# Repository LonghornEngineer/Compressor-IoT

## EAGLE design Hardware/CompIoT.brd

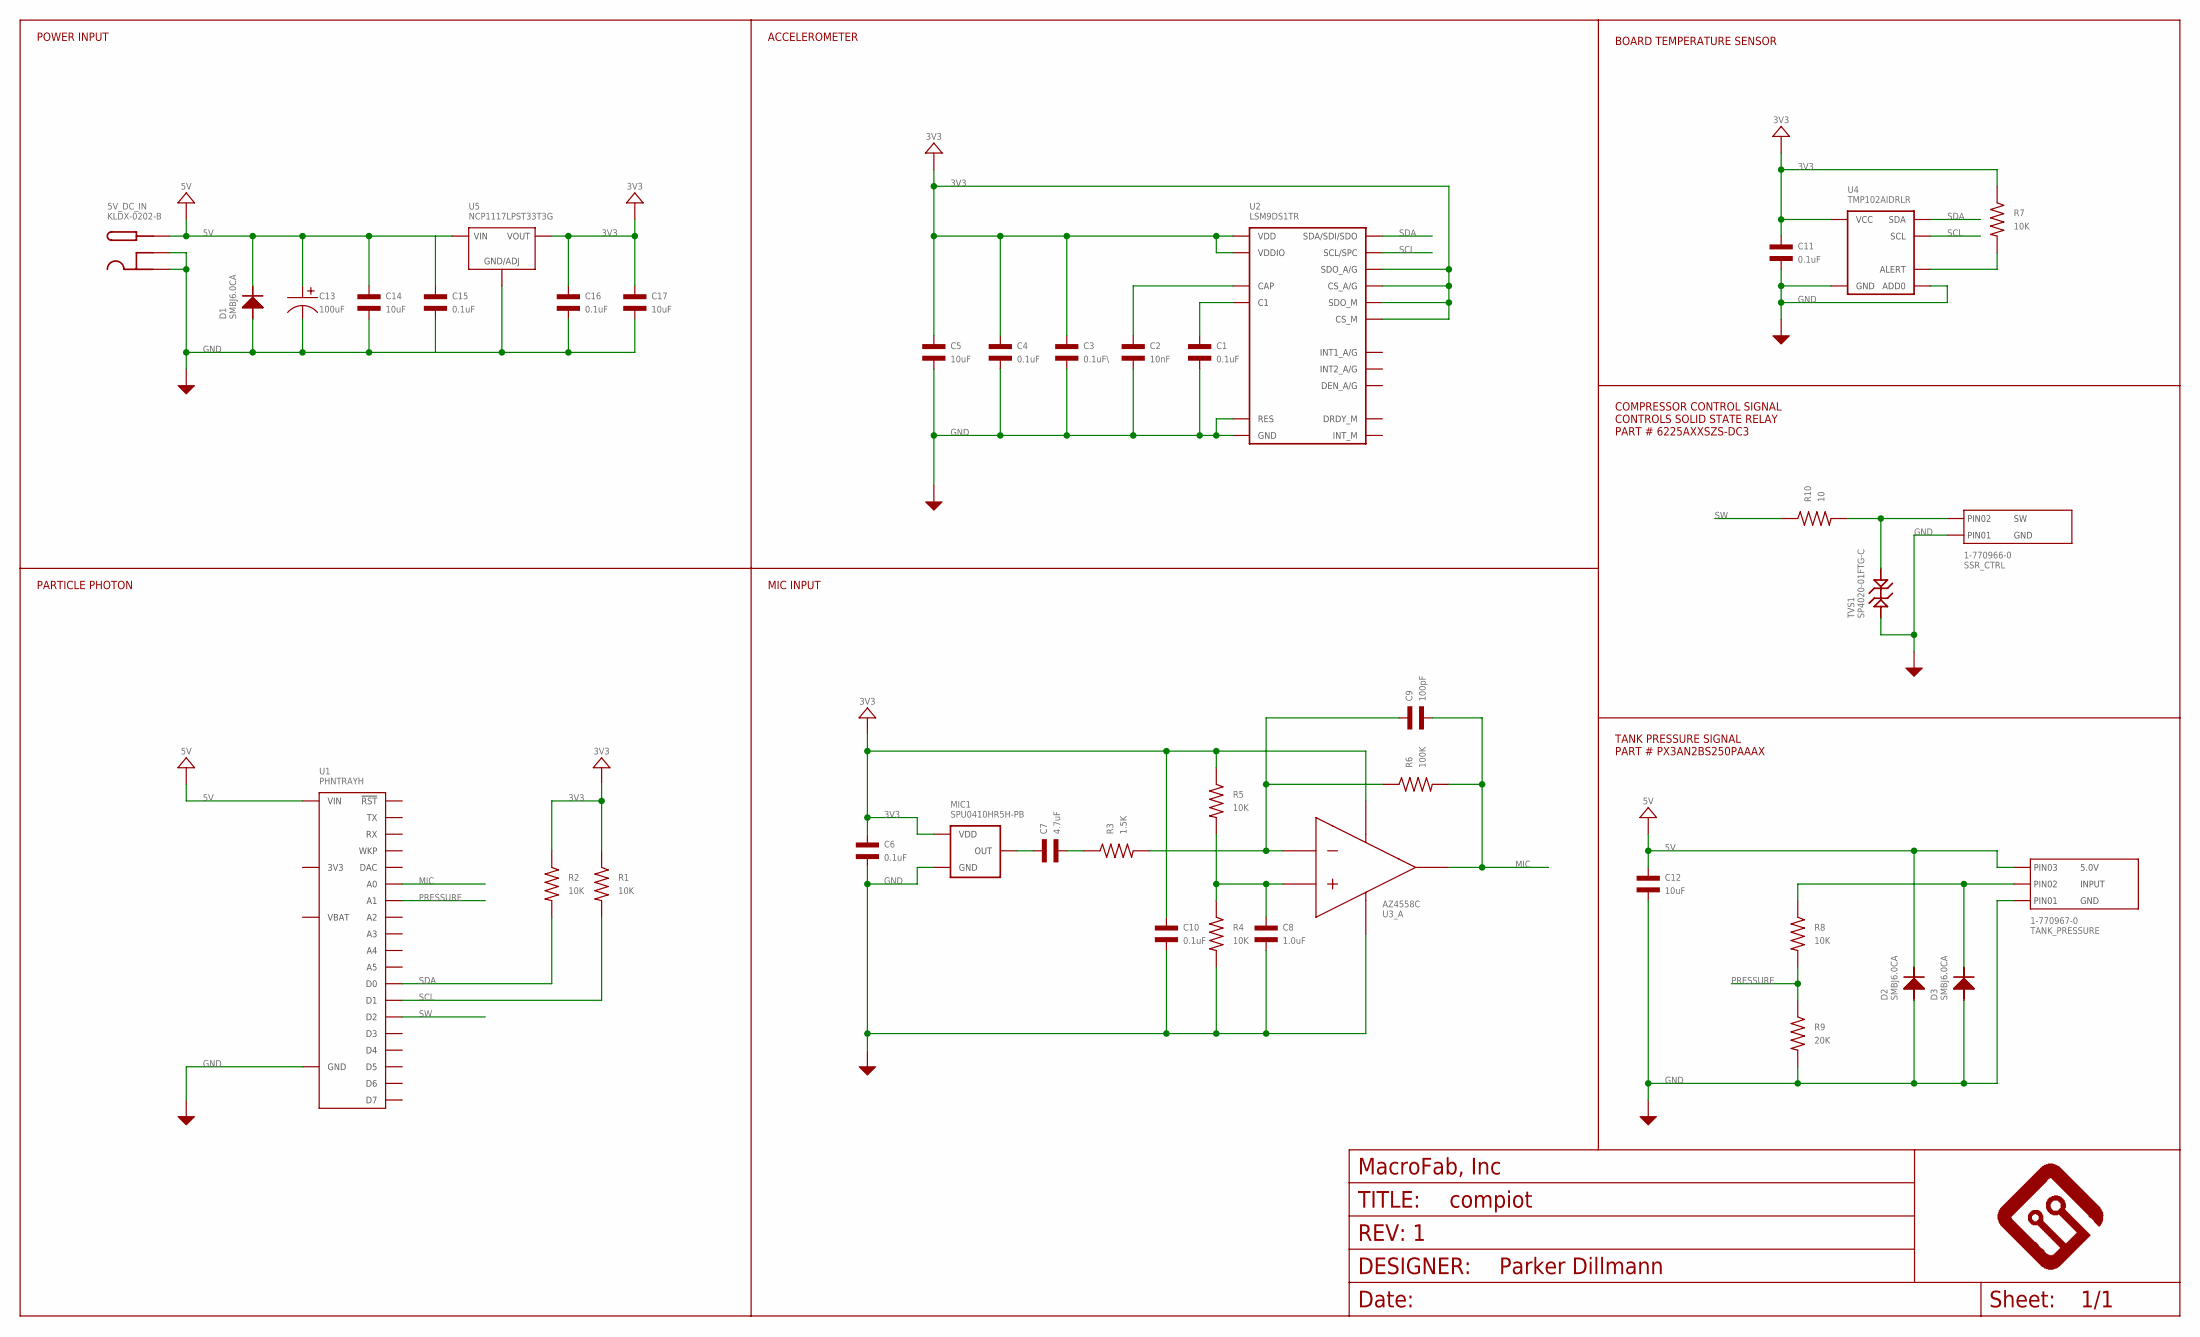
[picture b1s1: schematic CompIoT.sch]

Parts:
5V_DC_IN: KLDX-0202-B; DC_PWR_JACK
C1, C4, C6, C10, C11, C15, C16: 0.1uF; C0603
C2: 10nF; C0603
C3: 0.1uF\; C0603
C5, C12, C14, C17: 10uF; C1206
C7: 4.7uF; C1206
C8: 1.0uF; C0603
C9: 100pF; C0603
C13: 100uF; CP6.3MM
D1, D2, D3: SMBJ6.0CA; SMBJ
FRAME1: MF_FRAMEDEFAULT; MF_FRAME_DEFAULT
MIC1: SPU0410HR5H-PB
R1, R2, R4, R5, R7, R8: 10K; R0603
R3: 1.5K; R0603
R6: 100K; R0603
R9: 20K; R0603
R10: 10; R0603
SSR_CTRL: 1-770966-0
TANK_PRESSURE: 1-770967-0
TVS1: SP4020-01FTG-C; SOD-323
U1: PHNTRAYH; PARTICLE_PHOTON_PTH
U2: LSM9DS1TR; LSM9DS1_LGA-24
U3: AZ4558C; AZ4558C_SOIC-8
U4: TMP102AIDRLR; TMP102_SOT-553-6
U5: NCP1117LPST33T3G; SOT-223-3

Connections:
3V3: C3.P$1, C4.P$1, C5.P$1, C6.P$1, C10.P$1, C11.P$1, C16.P$1, C17.P$1, MIC1.P$1 (VDD), R1.P$1, R2.P$1, R5.P$1, R7.P$1, U2.1 (VDDIO), U2.3 (VDDIO), U2.5 (SDO_A/G), U2.6 (SDO_M), U2.7 (CS_A/G), U2.8 (CS_M), U2.22 (VDD), U2.23 (VDD), U3.4 (VEE), U4.5 (VCC), U5.P$1 (VOUT), U5.P$3 (VOUT)
5V: 5V_DC_IN.PIN, C12.P$1, C13.P$1, C14.P$1, C15.P$1, D1.CATH (CATHODE), D2.CATH (CATHODE), TANK_PRESSURE.P$3 (PIN3), U1.1 (VIN), U5.P$4 (VIN)
GND: 5V_DC_IN.SLEEVE1 (SLEEVE), 5V_DC_IN.SLEEVE2 (SLEEVE_SHUNT), C1.P$2, C2.P$2, C3.P$2, C4.P$2, C5.P$2, C6.P$2, C8.P$2, C10.P$2, C11.P$2, C12.P$2, C13.P$2, C14.P$2, C15.P$2, C16.P$2, C17.P$2, D1.ANODE, D2.ANODE, D3.ANODE, MIC1.P$2 (GND), MIC1.P$3 (GND), R4.P$2, R9.P$2, SSR_CTRL.P$1 (PIN1), TANK_PRESSURE.P$1 (PIN1), TVS1.ANODE, U1.2 (GND), U1.21 (GND), U2.14 (RES), U2.15 (RES), U2.16 (RES), U2.17 (RES), U2.18 (RES), U2.19 (GND), U2.20 (GND), U3.8 (VCC), U4.2 (GND), U4.4 (ADD0), U5.P$2 (GND/ADJ)
MIC: C9.P$2, R6.P$2, U1.12 (A0), U3.1 (OUTPUT_1)
unnamed: C1.P$1, U2.24 (C1)
unnamed: C2.P$1, U2.21 (CAP)
unnamed: C7.P$1, MIC1.P$4 (OUT)
unnamed: C7.P$2, R3.P$1
unnamed: C9.P$1, R3.P$2, R6.P$1, U3.2 (INPUT_1-)
unnamed: C8.P$1, R4.P$1, R5.P$2, U3.3 (INPUT_1+)
unnamed: R7.P$2, U4.3 (ALERT)
unnamed: R10.P$2, SSR_CTRL.P$2 (PIN2), TVS1.CATH
unnamed: D3.CATH (CATHODE), R8.P$1, TANK_PRESSURE.P$2 (PIN2)
PRESSURE: R8.P$2, R9.P$1, U1.11 (A1)
SCL: R1.P$2, U1.14 (D1), U2.2 (SCL/SPC), U4.1 (SCL)
SDA: R2.P$2, U1.13 (D0), U2.4 (SDA/SDI/SDO), U4.6 (SDA)
SW: R10.P$1, U1.15 (D2)

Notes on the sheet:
COMPRESSOR CONTROL SIGNAL CONTROLS SOLID STATE RELAY PART # 6225AXXSZS-DC3
TANK PRESSURE SIGNAL PART # PX3AN2BS250PAAAX
BOARD TEMPERATURE SENSOR
ACCELEROMETER
MIC INPUT
POWER INPUT
PARTICLE PHOTON

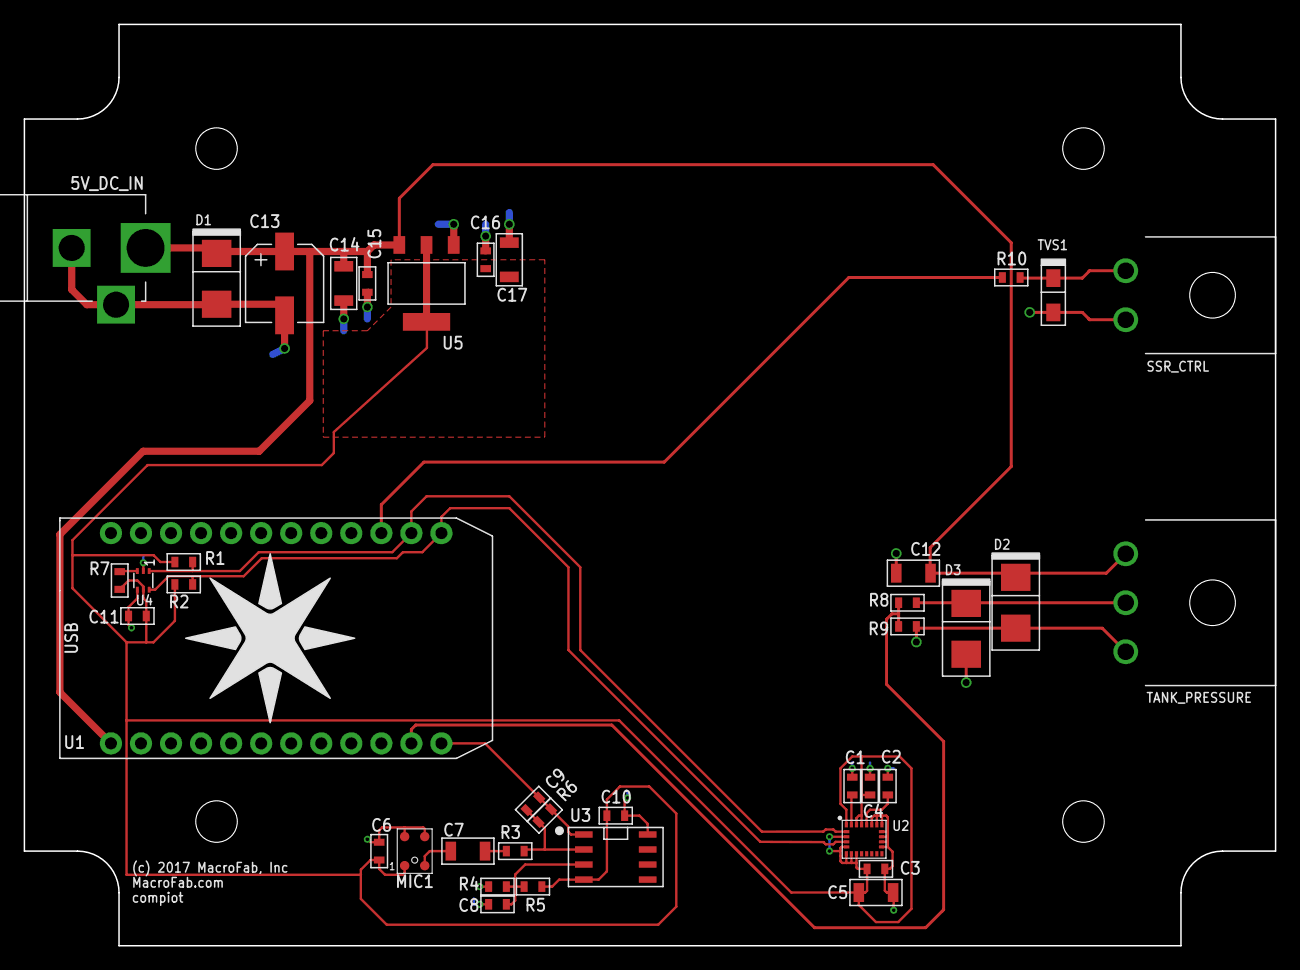
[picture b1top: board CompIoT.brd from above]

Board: 2 copper layers, 105.8 x 77.9 mm, 41 parts (0 on the bottom side), 17 nets.

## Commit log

2018-06-06 First Push
2018-06-06 cleaned up schematic

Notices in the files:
parts and their libraries:
MF_Aesthetics: (c) 2017 MacroFab, Inc
